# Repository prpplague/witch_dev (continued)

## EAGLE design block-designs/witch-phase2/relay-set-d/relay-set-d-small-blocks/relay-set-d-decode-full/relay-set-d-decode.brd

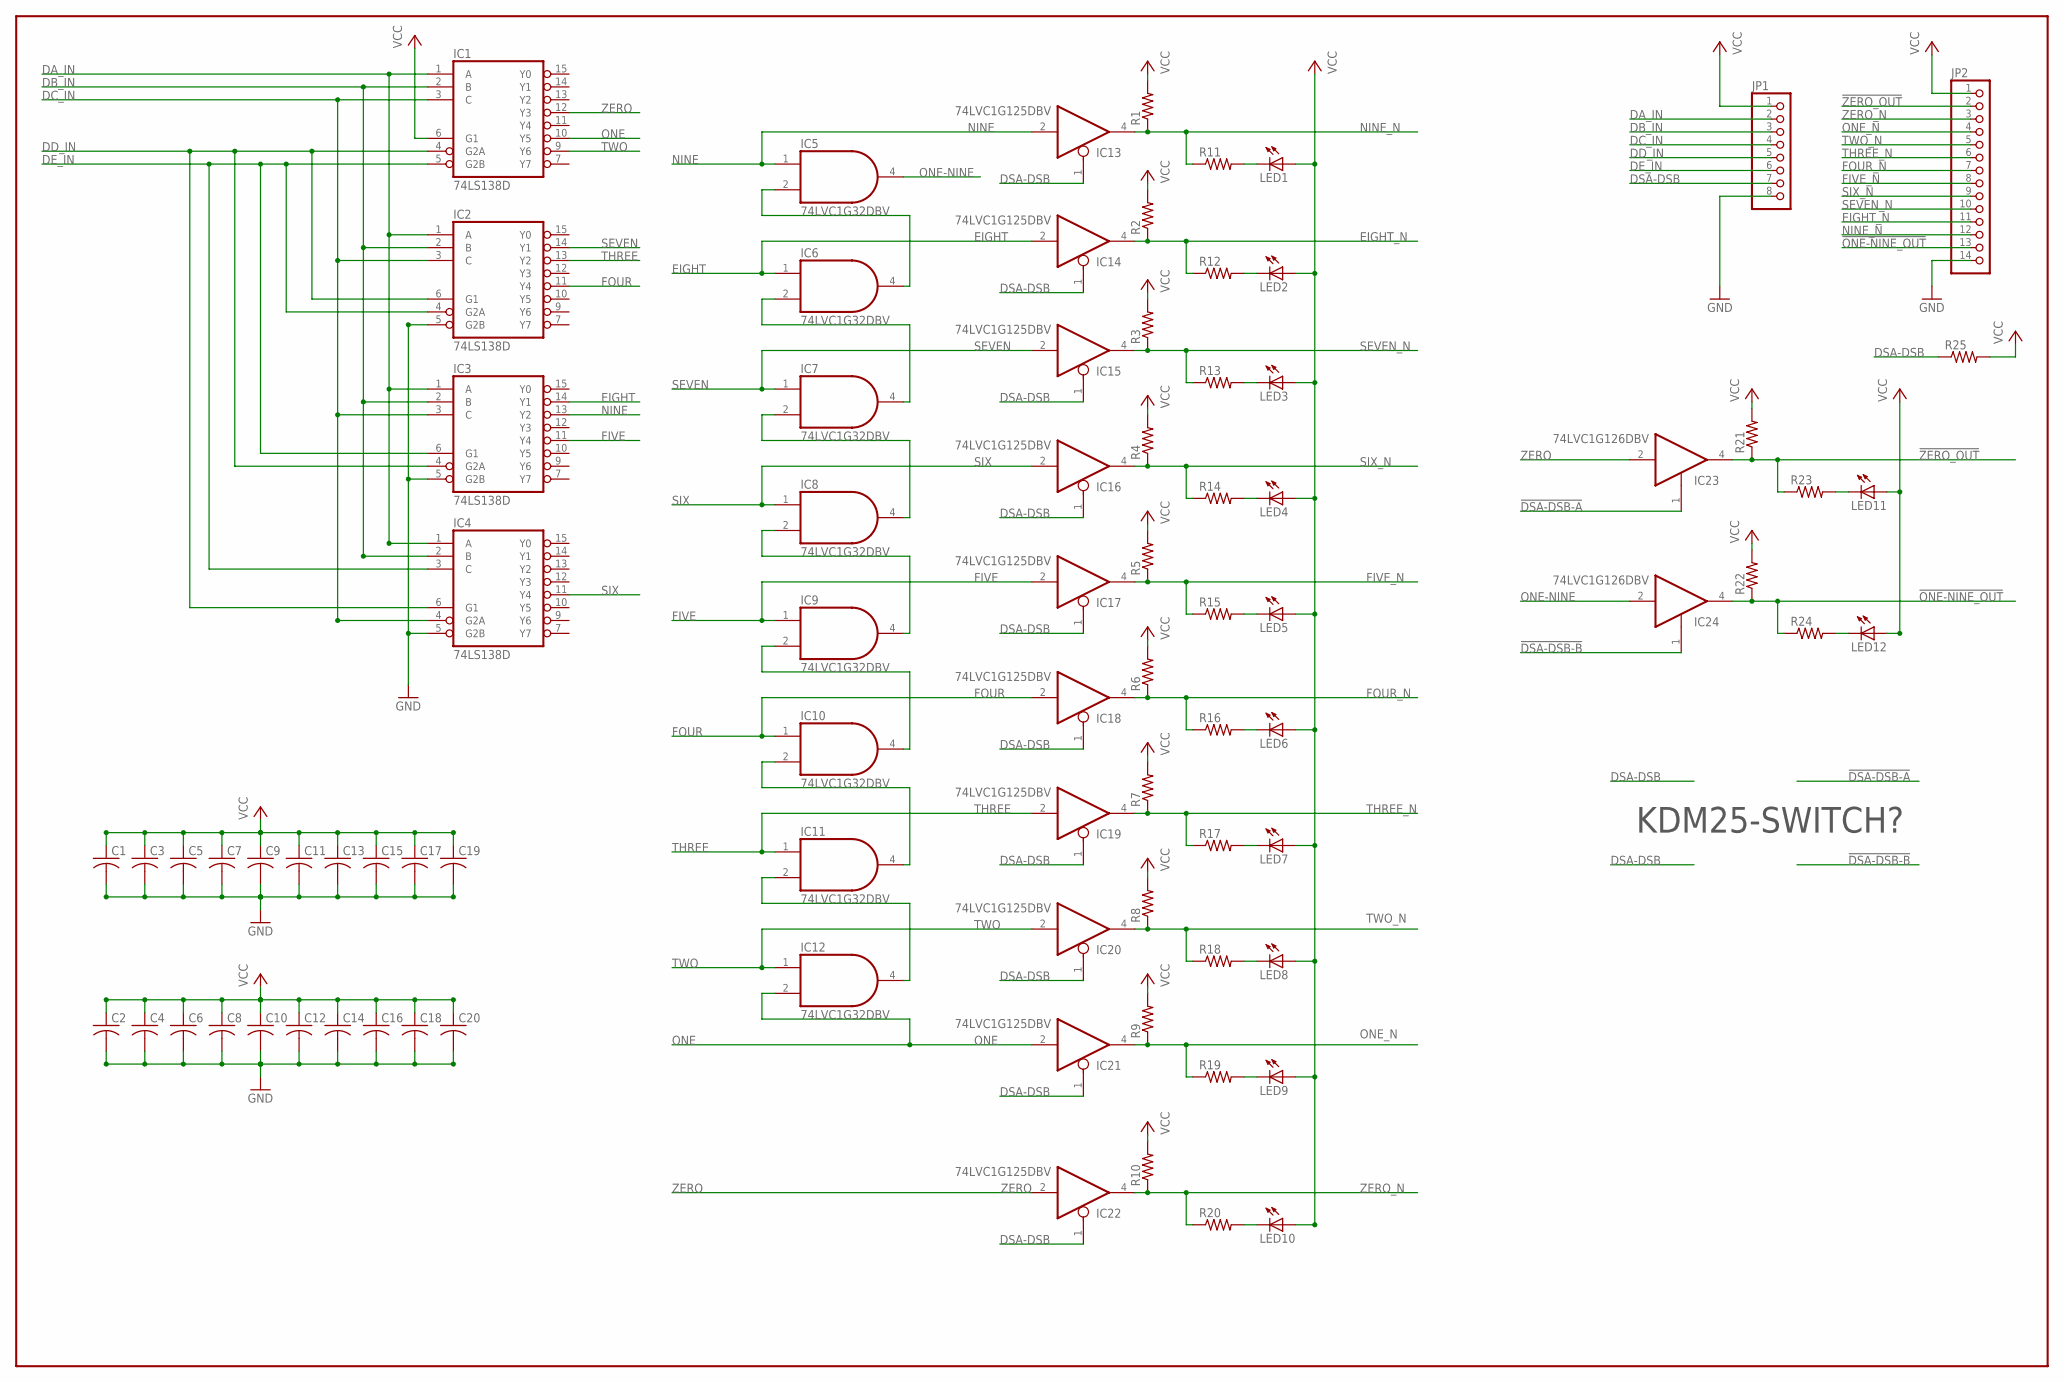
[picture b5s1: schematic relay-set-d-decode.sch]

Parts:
C1, C2, C3, C4, C5, C6, C7, C8, C9, C10, C11, C12, C13, C14, C15, C16, C17, C18, C19, C20: C-USC0805; C0805
IC1, IC2, IC3, IC4: 74LS138D; SO16
IC5, IC6, IC7, IC8, IC9, IC10, IC11, IC12: 74LVC1G32DBV; SOT23-5
IC13, IC14, IC15, IC16, IC17, IC18, IC19, IC20, IC21, IC22: 74LVC1G125DBV; SOT23-5
IC23, IC24: 74LVC1G126DBV; SOT23-5
JP1: PINHD-1X8; 1X08
JP2: PINHD-1X14; 1X14
LED1, LED2, LED3, LED4, LED5, LED6, LED7, LED8, LED9, LED10, LED11, LED12: LEDCHIP-LED0805; CHIP-LED0805
R1, R2, R3, R4, R5, R6, R7, R8, R9, R10, R11, R12, R13, R14, R15, R16, R17, R18, R19, R20, R21, R22, R23, R24, R25: R-US_R0805; R0805

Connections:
!DSA-DSB-A: IC23.1 (OE)
!DSA-DSB-B: IC24.1 (OE)
!ONE-NINE_OUT: IC24.4 (O), JP2.13, R22.1, R24.1
!ZERO_OUT: IC23.4 (O), JP2.2, R21.1, R23.1
DA_IN: IC1.1 (A), IC2.1 (A), IC3.1 (A), IC4.1 (A), JP1.2
DB_IN: IC1.2 (B), IC2.2 (B), IC3.2 (B), IC4.2 (B), JP1.3
DC_IN: IC1.3 (C), IC2.3 (C), IC3.3 (C), IC4.4 (G2A), JP1.4
DD_IN: IC1.4 (G2A), IC2.6 (G1), IC3.4 (G2A), IC4.6 (G1), JP1.5
DE_IN: IC1.5 (G2B), IC2.4 (G2A), IC3.6 (G1), IC4.3 (C), JP1.6
DSA-DSB: IC13.1 (OE), IC14.1 (OE), IC15.1 (OE), IC16.1 (OE), IC17.1 (OE), IC18.1 (OE), IC19.1 (OE), IC20.1 (OE), IC21.1 (OE), IC22.1 (OE), JP1.7, R25.1
EIGHT: IC3.14 (Y1), IC6.1 (I0), IC14.2 (I)
EIGHT_N: IC14.4 (O), JP2.11, R2.1, R12.1
FIVE: IC3.11 (Y4), IC9.1 (I0), IC17.2 (I)
FIVE_N: IC17.4 (O), JP2.8, R5.1, R15.1
FOUR: IC2.11 (Y4), IC10.1 (I0), IC18.2 (I)
FOUR_N: IC18.4 (O), JP2.7, R6.1, R16.1
GND: C1.2, C2.2, C3.2, C4.2, C5.2, C6.2, C7.2, C8.2, C9.2, C10.2, C11.2, C12.2, C13.2, C14.2, C15.2, C16.2, C17.2, C18.2, C19.2, C20.2, IC1.8 (GND), IC2.5 (G2B), IC2.8 (GND), IC3.5 (G2B), IC3.8 (GND), IC4.5 (G2B), IC4.8 (GND), IC5.3 (GND), IC6.3 (GND), IC7.3 (GND), IC8.3 (GND), IC9.3 (GND), IC10.3 (GND), IC11.3 (GND), IC12.3 (GND), IC13.3 (GND), IC14.3 (GND), IC15.3 (GND), IC16.3 (GND), IC17.3 (GND), IC18.3 (GND), IC19.3 (GND), IC20.3 (GND), IC21.3 (GND), IC22.3 (GND), IC23.3 (GND), IC24.3 (GND), JP1.8, JP2.14
unnamed: LED1.C, R11.2
unnamed: LED2.C, R12.2
unnamed: LED3.C, R13.2
unnamed: LED4.C, R14.2
unnamed: LED5.C, R15.2
unnamed: LED6.C, R16.2
unnamed: LED7.C, R17.2
unnamed: LED8.C, R18.2
unnamed: LED9.C, R19.2
unnamed: LED10.C, R20.2
unnamed: IC8.2 (I1), IC9.4 (O)
unnamed: IC9.2 (I1), IC10.4 (O)
unnamed: IC10.2 (I1), IC11.4 (O)
unnamed: IC11.2 (I1), IC12.4 (O)
unnamed: LED11.C, R23.2
unnamed: IC5.2 (I1), IC6.4 (O)
unnamed: IC6.2 (I1), IC7.4 (O)
unnamed: IC7.2 (I1), IC8.4 (O)
unnamed: LED12.C, R24.2
NINE: IC3.13 (Y2), IC5.1 (I0), IC13.2 (I)
NINE_N: IC13.4 (O), JP2.12, R1.1, R11.1
ONE: IC1.10 (Y5), IC12.2 (I1), IC21.2 (I)
ONE-NINE: IC5.4 (O), IC24.2 (I)
ONE_N: IC21.4 (O), JP2.4, R9.1, R19.1
SEVEN: IC2.14 (Y1), IC7.1 (I0), IC15.2 (I)
SEVEN_N: IC15.4 (O), JP2.10, R3.1, R13.1
SIX: IC4.11 (Y4), IC8.1 (I0), IC16.2 (I)
SIX_N: IC16.4 (O), JP2.9, R4.1, R14.1
THREE: IC2.13 (Y2), IC11.1 (I0), IC19.2 (I)
THREE_N: IC19.4 (O), JP2.6, R7.1, R17.1
TWO: IC1.9 (Y6), IC12.1 (I0), IC20.2 (I)
TWO_N: IC20.4 (O), JP2.5, R8.1, R18.1
VCC: C1.1, C2.1, C3.1, C4.1, C5.1, C6.1, C7.1, C8.1, C9.1, C10.1, C11.1, C12.1, C13.1, C14.1, C15.1, C16.1, C17.1, C18.1, C19.1, C20.1, IC1.6 (G1), IC1.16 (VCC), IC2.16 (VCC), IC3.16 (VCC), IC4.16 (VCC), IC5.5 (VCC), IC6.5 (VCC), IC7.5 (VCC), IC8.5 (VCC), IC9.5 (VCC), IC10.5 (VCC), IC11.5 (VCC), IC12.5 (VCC), IC13.5 (VCC), IC14.5 (VCC), IC15.5 (VCC), IC16.5 (VCC), IC17.5 (VCC), IC18.5 (VCC), IC19.5 (VCC), IC20.5 (VCC), IC21.5 (VCC), IC22.5 (VCC), IC23.5 (VCC), IC24.5 (VCC), JP1.1, JP2.1, LED1.A, LED2.A, LED3.A, LED4.A, LED5.A, LED6.A, LED7.A, LED8.A, LED9.A, LED10.A, LED11.A, LED12.A, R1.2, R2.2, R3.2, R4.2, R5.2, R6.2, R7.2, R8.2, R9.2, R10.2, R21.2, R22.2, R25.2
ZERO: IC1.12 (Y3), IC22.2 (I), IC23.2 (I)
ZERO_N: IC22.4 (O), JP2.3, R10.1, R20.1

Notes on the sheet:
KDM25-SWITCH?

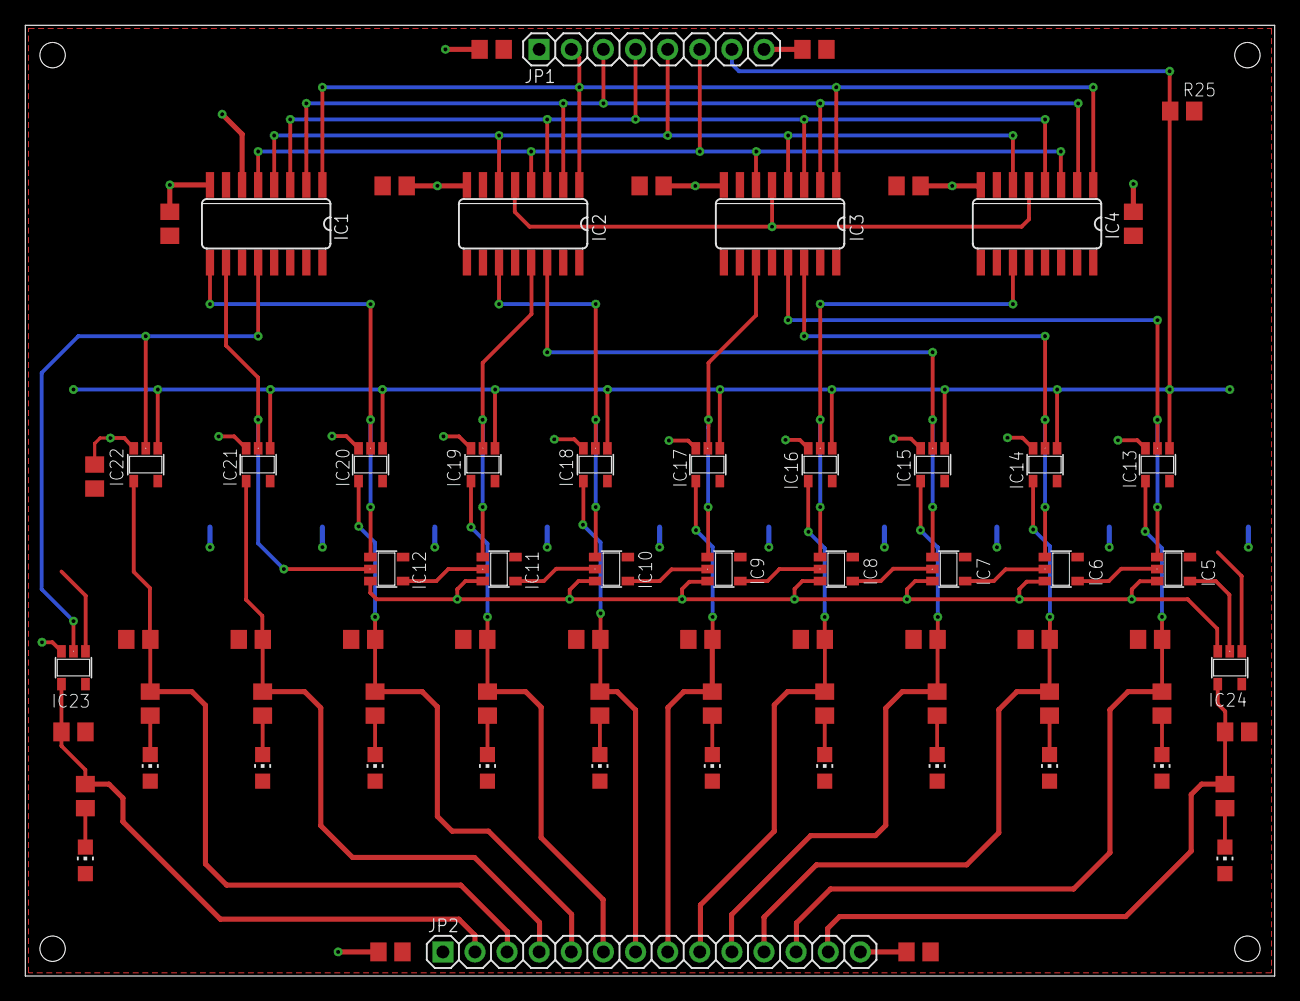
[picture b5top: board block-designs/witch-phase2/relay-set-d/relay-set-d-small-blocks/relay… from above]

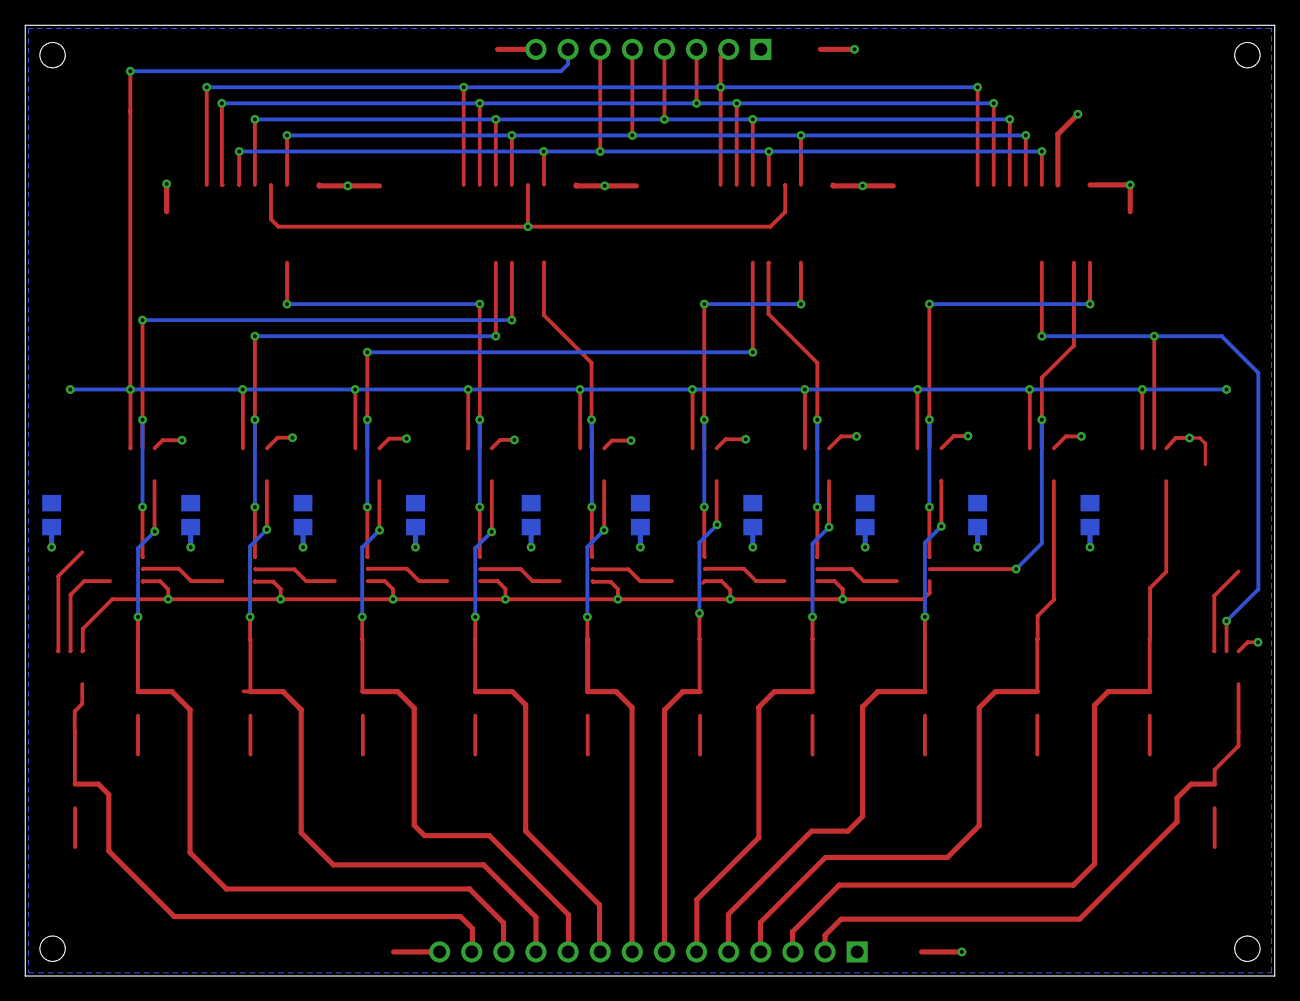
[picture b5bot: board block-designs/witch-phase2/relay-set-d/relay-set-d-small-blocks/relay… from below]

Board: 2 copper layers, 98.8 x 75.2 mm, 83 parts (10 on the bottom side), 50 nets.

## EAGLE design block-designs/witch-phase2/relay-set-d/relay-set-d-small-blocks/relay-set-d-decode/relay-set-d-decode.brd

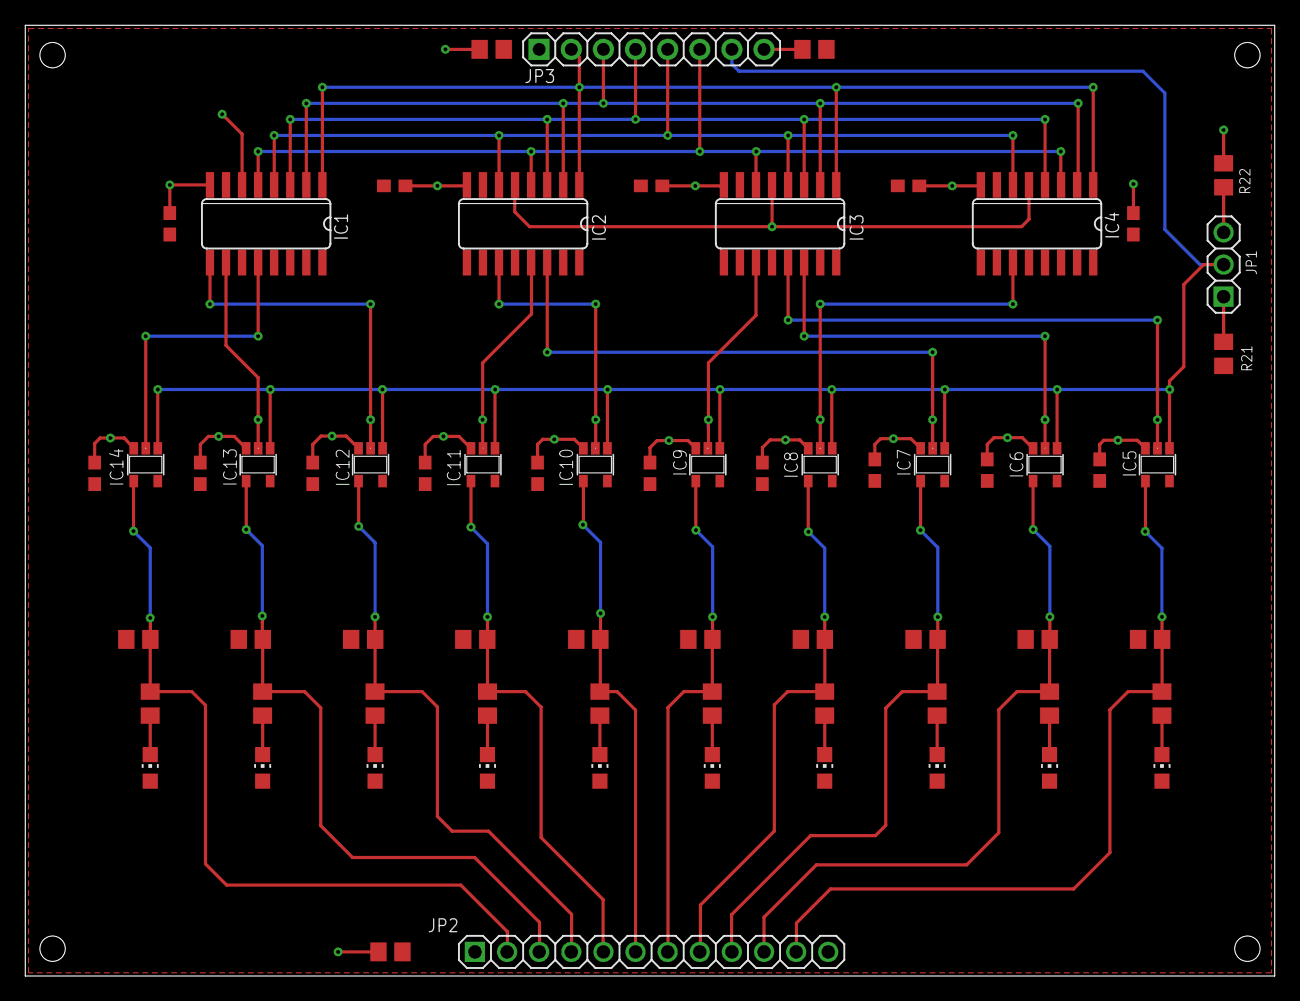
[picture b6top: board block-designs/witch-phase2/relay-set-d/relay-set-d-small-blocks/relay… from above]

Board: 2 copper layers, 98.8 x 75.2 mm, 67 parts (0 on the bottom side), 40 nets.

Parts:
C1, C2, C3, C4, C6, C8, C10, C11, C12, C13, C14, C15, C16, C17, C18: C0603
C5, C7, C9: C0805
IC1, IC2, IC3, IC4: 74LS138D; SO16
IC5, IC6, IC7, IC8, IC9, IC10, IC11, IC12, IC13, IC14: 74LVC1G125DBV; SOT23-5
JP1: 1X03
JP2: 1X12
JP3: 1X08
LED1, LED2, LED3, LED4, LED5, LED6, LED7, LED8, LED9, LED10: CHIP-LED0805
R1, R2, R3, R4, R5, R6, R7, R8, R9, R10, R11, R12, R13, R14, R15, R16, R17, R18, R19, R20, R21, R22: R0805

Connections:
DA_IN: IC1.1, IC2.1, IC3.1, IC4.1, JP3.2
DB_IN: IC1.2, IC2.2, IC3.2, IC4.2, JP3.3
DC_IN: IC1.3, IC2.3, IC3.3, IC4.4, JP3.4
DD_IN: IC1.4, IC2.6, IC3.4, IC4.6, JP3.5
DE_IN: IC1.5, IC2.4, IC3.6, IC4.3, JP3.6
DSA-DSB: IC5.1, IC6.1, IC7.1, IC8.1, IC9.1, IC10.1, IC11.1, IC12.1, IC13.1, IC14.1, JP1.2, JP3.7
EIGHT: IC3.14, IC6.2
EIGHT_N: IC6.4, JP2.10, R2.1, R12.1
FIVE: IC3.11, IC9.2
FIVE_N: IC9.4, JP2.7, R5.1, R15.1
FOUR: IC2.11, IC10.2
FOUR_N: IC10.4, JP2.6, R6.1, R16.1
GND: C1.2, C2.2, C3.2, C4.2, C5.2, C6.2, C7.2, C8.2, C9.2, C10.2, C11.2, C12.2, C13.2, C14.2, C15.2, C16.2, C17.2, C18.2, IC1.8, IC2.5, IC2.8, IC3.5, IC3.8, IC4.5, IC4.8, IC5.3, IC6.3, IC7.3, IC8.3, IC9.3, IC10.3, IC11.3, IC12.3, IC13.3, IC14.3, JP2.1, JP2.12, JP3.8, R22.1
unnamed: LED1.C, R11.2
unnamed: LED2.C, R12.2
unnamed: LED3.C, R13.2
unnamed: LED4.C, R14.2
unnamed: LED5.C, R15.2
unnamed: LED6.C, R16.2
unnamed: LED7.C, R17.2
unnamed: LED8.C, R18.2
unnamed: LED9.C, R19.2
unnamed: LED10.C, R20.2
unnamed: JP1.1, R21.1
unnamed: JP1.3, R22.2
NINE: IC3.13, IC5.2
NINE_N: IC5.4, JP2.11, R1.1, R11.1
ONE: IC1.10, IC13.2
ONE_N: IC13.4, JP2.3, R9.1, R19.1
SEVEN: IC2.14, IC7.2
SEVEN_N: IC7.4, JP2.9, R3.1, R13.1
SIX: IC4.11, IC8.2
SIX_N: IC8.4, JP2.8, R4.1, R14.1
THREE: IC2.13, IC11.2
THREE_N: IC11.4, JP2.5, R7.1, R17.1
TWO: IC1.9, IC12.2
TWO_N: IC12.4, JP2.4, R8.1, R18.1
VCC: C1.1, C2.1, C3.1, C4.1, C5.1, C6.1, C7.1, C8.1, C9.1, C10.1, C11.1, C12.1, C13.1, C14.1, C15.1, C16.1, C17.1, C18.1, IC1.6, IC1.16, IC2.16, IC3.16, IC4.16, IC5.5, IC6.5, IC7.5, IC8.5, IC9.5, IC10.5, IC11.5, IC12.5, IC13.5, IC14.5, JP3.1, LED1.A, LED2.A, LED3.A, LED4.A, LED5.A, LED6.A, LED7.A, LED8.A, LED9.A, LED10.A, R1.2, R2.2, R3.2, R4.2, R5.2, R6.2, R7.2, R8.2, R9.2, R10.2, R21.2
ZERO: IC1.12, IC14.2
ZERO_N: IC14.4, JP2.2, R10.1, R20.1

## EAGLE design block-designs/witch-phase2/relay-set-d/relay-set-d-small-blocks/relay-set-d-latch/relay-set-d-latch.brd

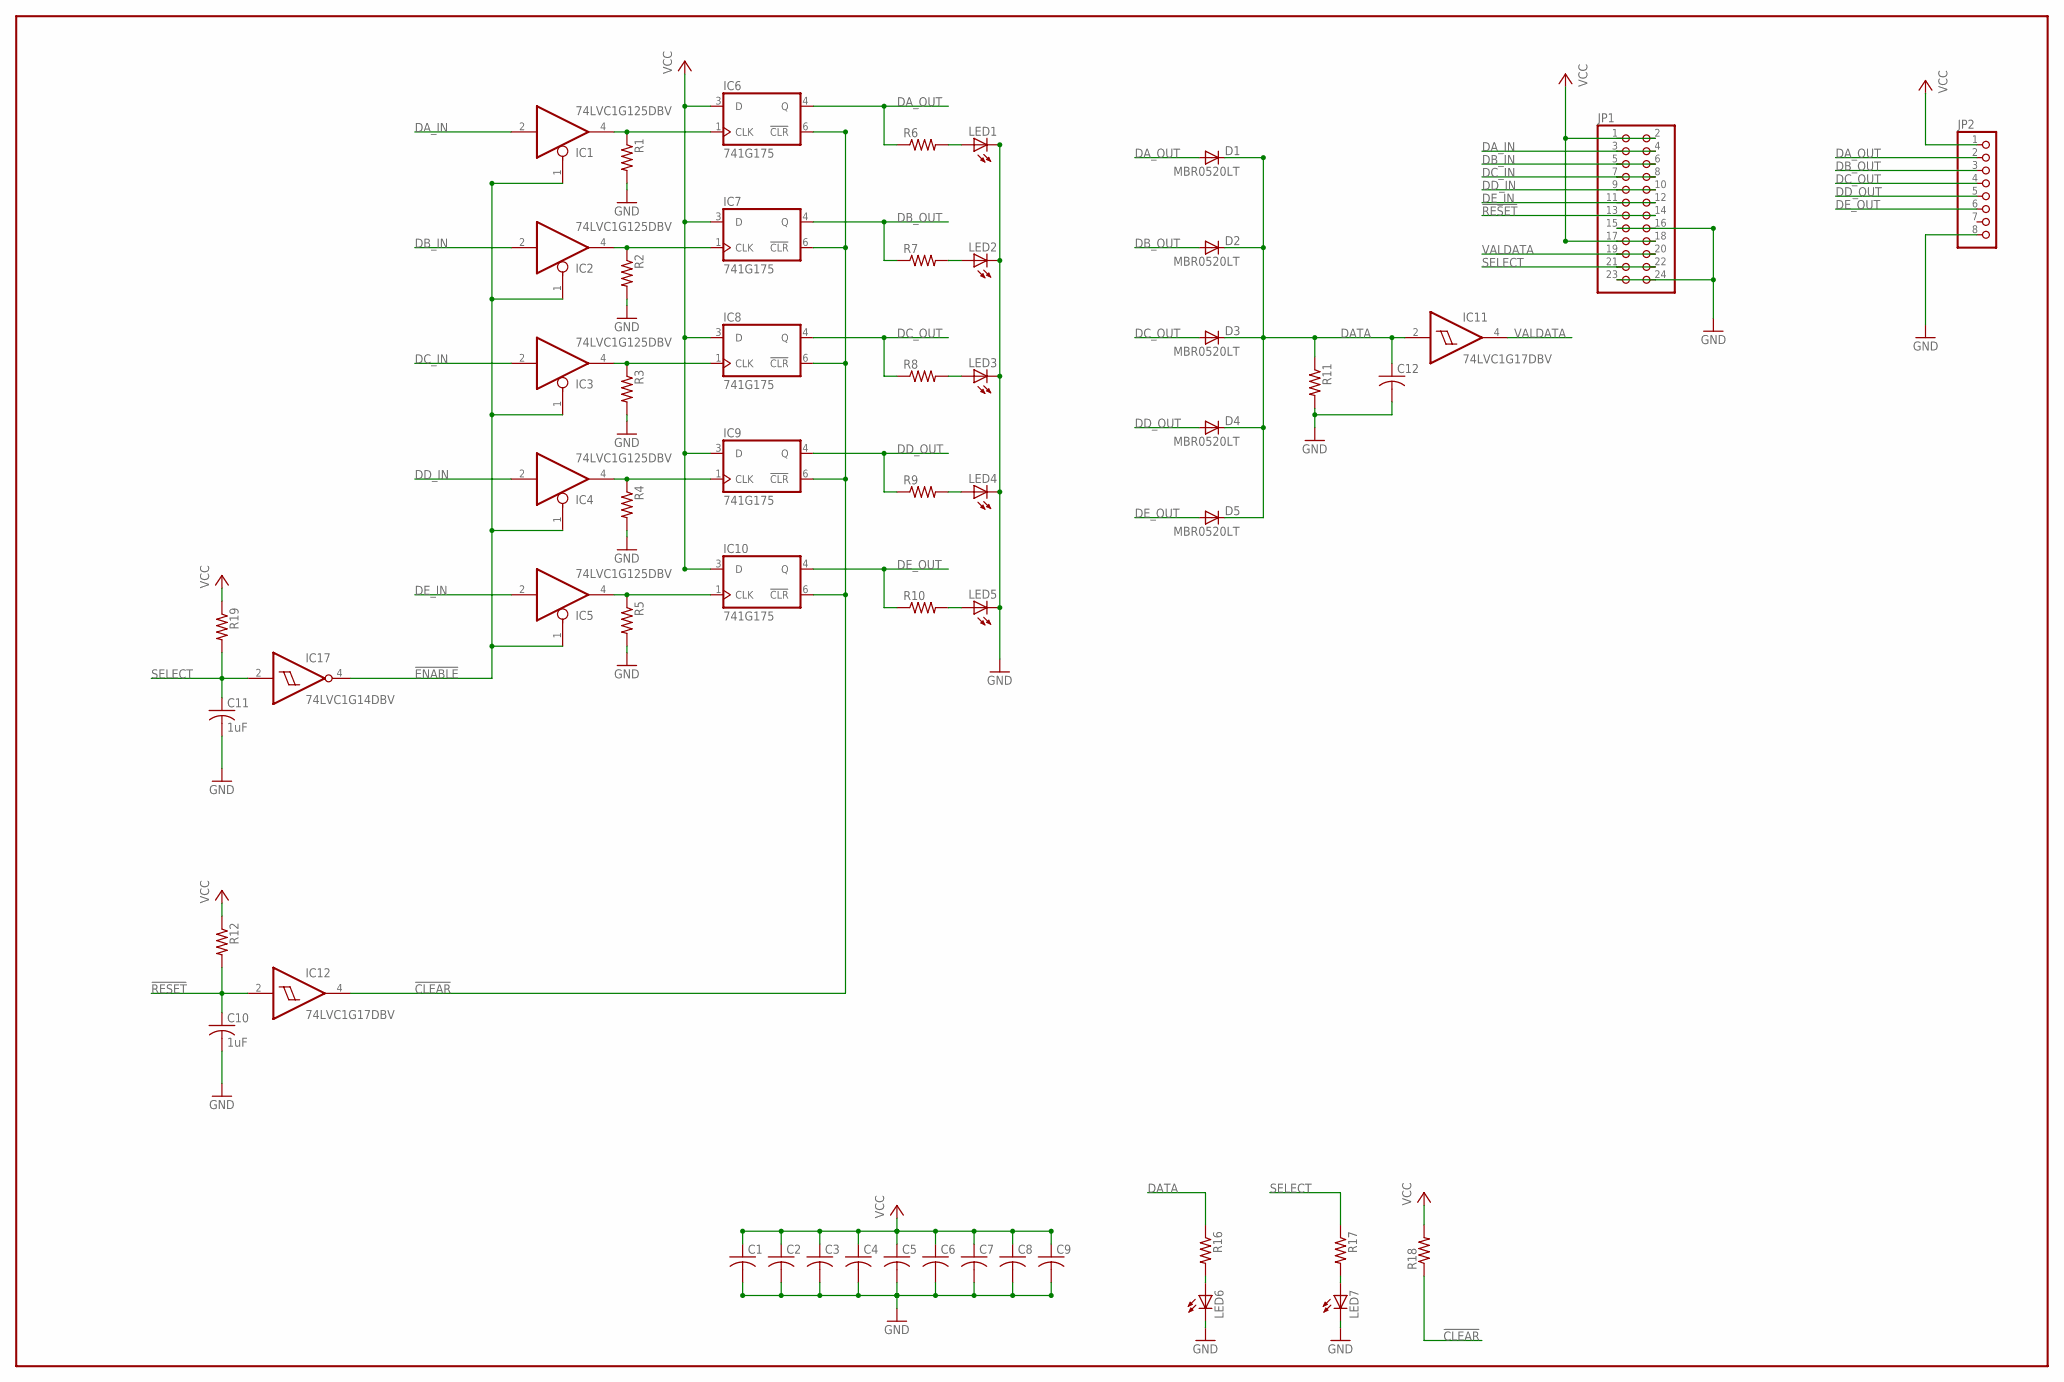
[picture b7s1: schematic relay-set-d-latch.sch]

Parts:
C1, C2, C3, C4, C12: C-USC0805; C0805
C5, C6, C7, C8, C9: C-USC0603K; C0603K
C10, C11: 1uF; C0603K
D1, D2, D3, D4, D5: MBR0520LT; SOD123
IC1, IC2, IC3, IC4, IC5: 74LVC1G125DBV; SOT23-5
IC6, IC7, IC8, IC9, IC10: 741G175; DBV_R-PDSO-G6
IC11, IC12: 74LVC1G17DBV; SOT23-5
IC17: 74LVC1G14DBV; SOT23-5
JP1: PINHD-2X12; 2X12
JP2: PINHD-1X8; 1X08
LED1, LED2, LED3, LED4, LED5, LED6, LED7: LEDCHIP-LED0805; CHIP-LED0805
R1, R2, R3, R4, R5, R6, R7, R8, R9, R10, R11, R12, R16, R17, R18, R19: R-US_R0805; R0805

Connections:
!CLEAR: IC6.6 (!CLR), IC7.6 (!CLR), IC8.6 (!CLR), IC9.6 (!CLR), IC10.6 (!CLR), IC12.4 (O), R18.1
!ENABLE: IC1.1 (OE), IC2.1 (OE), IC3.1 (OE), IC4.1 (OE), IC5.1 (OE), IC17.4 (O)
!RESET: C10.1, IC12.2 (I), JP1.13, JP1.14, R12.2
DA: IC1.4 (O), IC6.1 (CLK), R1.1
DATA: C12.1, D1.C, D2.C, D3.C, D4.C, D5.C, IC11.2 (I), R11.1, R16.1
DA_IN: IC1.2 (I), JP1.3, JP1.4
DA_OUT: D1.A, IC6.4 (Q), JP2.2, R6.1
DB: IC2.4 (O), IC7.1 (CLK), R2.1
DB_IN: IC2.2 (I), JP1.5, JP1.6
DB_OUT: D2.A, IC7.4 (Q), JP2.3, R7.1
DC: IC3.4 (O), IC8.1 (CLK), R3.1
DC_IN: IC3.2 (I), JP1.7, JP1.8
DC_OUT: D3.A, IC8.4 (Q), JP2.4, R8.1
DD: IC4.4 (O), IC9.1 (CLK), R4.1
DD_IN: IC4.2 (I), JP1.9, JP1.10
DD_OUT: D4.A, IC9.4 (Q), JP2.5, R9.1
DE: IC5.4 (O), IC10.1 (CLK), R5.1
DE_IN: IC5.2 (I), JP1.11, JP1.12
DE_OUT: D5.A, IC10.4 (Q), JP2.6, R10.1
GND: C1.2, C2.2, C3.2, C4.2, C5.2, C6.2, C7.2, C8.2, C9.2, C10.2, C11.2, C12.2, IC1.3 (GND), IC2.3 (GND), IC3.3 (GND), IC4.3 (GND), IC5.3 (GND), IC6.2 (GND), IC7.2 (GND), IC8.2 (GND), IC9.2 (GND), IC10.2 (GND), IC11.3 (GND), IC12.3 (GND), IC17.3 (GND), JP1.15, JP1.16, JP1.23, JP1.24, JP2.8, LED1.C, LED2.C, LED3.C, LED4.C, LED5.C, LED6.C, LED7.C, R1.2, R2.2, R3.2, R4.2, R5.2, R11.2
unnamed: LED1.A, R6.2
unnamed: LED2.A, R7.2
unnamed: LED3.A, R8.2
unnamed: LED7.A, R17.2
unnamed: LED6.A, R16.2
unnamed: LED4.A, R9.2
unnamed: LED5.A, R10.2
SELECT: C11.1, IC17.2 (I), JP1.21, JP1.22, R17.1, R19.2
VALDATA: IC11.4 (O), JP1.19, JP1.20
VCC: C1.1, C2.1, C3.1, C4.1, C5.1, C6.1, C7.1, C8.1, C9.1, IC1.5 (VCC), IC2.5 (VCC), IC3.5 (VCC), IC4.5 (VCC), IC5.5 (VCC), IC6.3 (D), IC6.5 (VCC), IC7.3 (D), IC7.5 (VCC), IC8.3 (D), IC8.5 (VCC), IC9.3 (D), IC9.5 (VCC), IC10.3 (D), IC10.5 (VCC), IC11.5 (VCC), IC12.5 (VCC), IC17.5 (VCC), JP1.1, JP1.2, JP1.17, JP1.18, JP2.1, R12.1, R18.2, R19.1

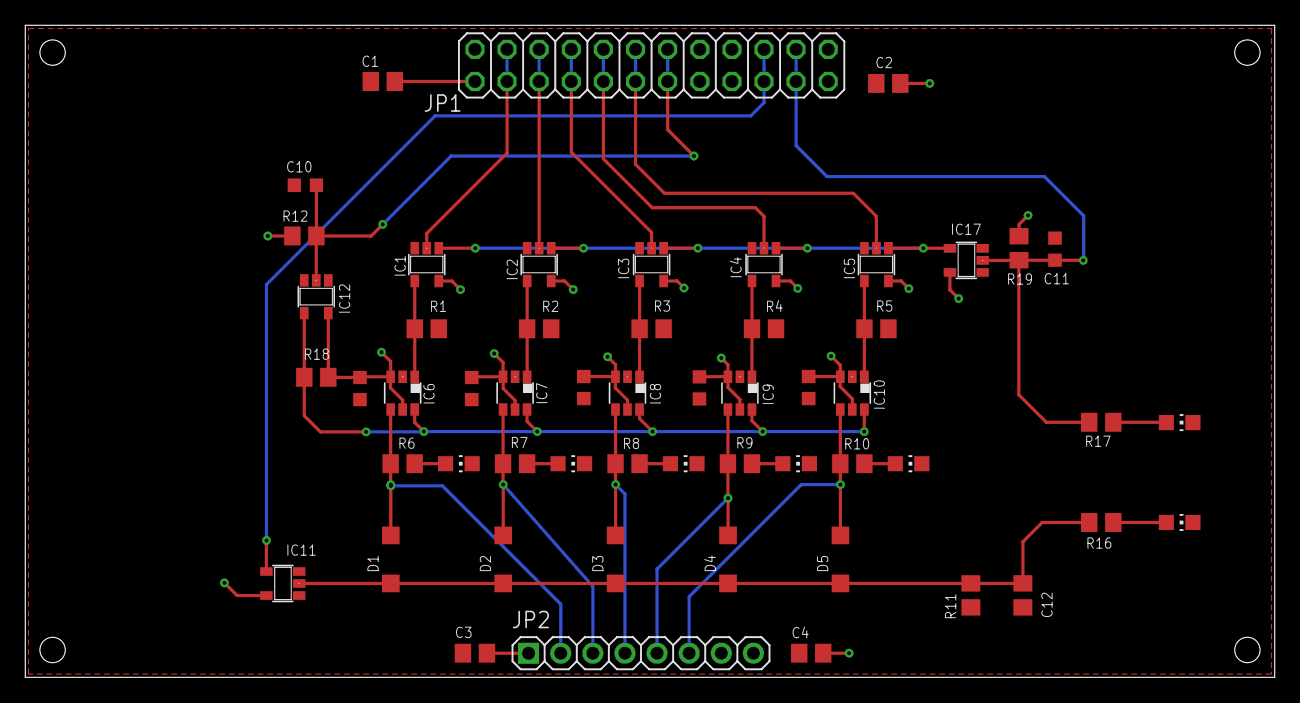
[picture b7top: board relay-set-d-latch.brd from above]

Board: 2 copper layers, 98.8 x 51.6 mm, 55 parts (0 on the bottom side), 30 nets.

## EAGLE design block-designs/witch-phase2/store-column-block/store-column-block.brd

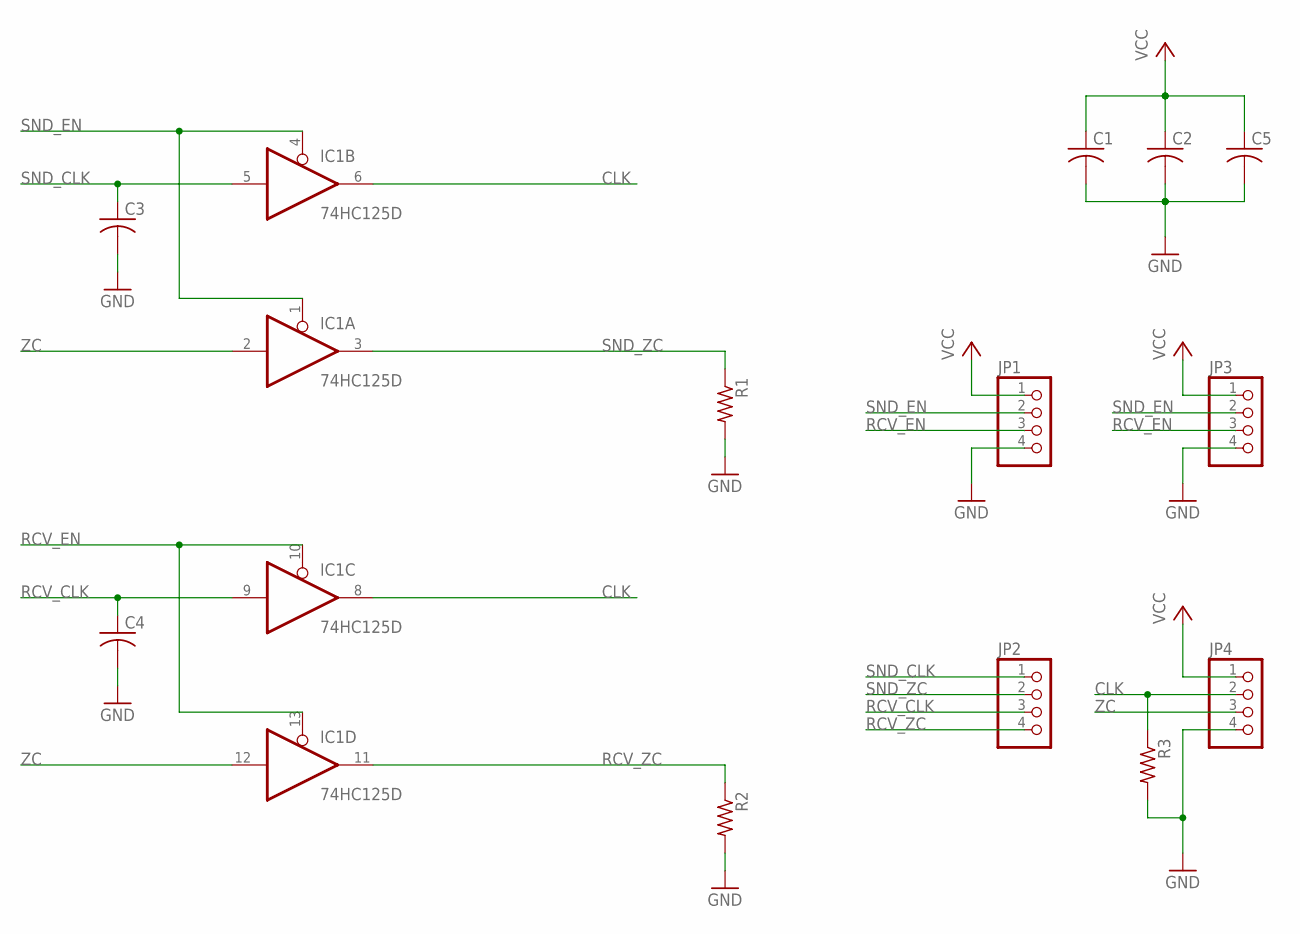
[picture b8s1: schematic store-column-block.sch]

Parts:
C1, C2, C3, C4, C5: C-USC0603K; C0603K
IC1: 74HC125D; SO14
JP1, JP2, JP3, JP4: PINHD-1X4; 1X04
R1, R2, R3: R-US_R0603; R0603

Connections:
CLK: IC1.6 (O), IC1.8 (O), JP4.2, R3.1
GND: C1.2, C2.2, C3.2, C4.2, C5.2, IC1.7 (GND), JP1.4, JP3.4, JP4.4, R1.2, R2.2, R3.2
RCV_CLK: C4.1, IC1.9 (I), JP2.3
RCV_EN: IC1.10 (OE), IC1.13 (OE), JP1.3, JP3.3
RCV_ZC: IC1.11 (O), JP2.4, R2.1
SND_CLK: C3.1, IC1.5 (I), JP2.1
SND_EN: IC1.1 (OE), IC1.4 (OE), JP1.2, JP3.2
SND_ZC: IC1.3 (O), JP2.2, R1.1
VCC: C1.1, C2.1, C5.1, IC1.14 (VCC), JP1.1, JP3.1, JP4.1
ZC: IC1.2 (I), IC1.12 (I), JP4.3

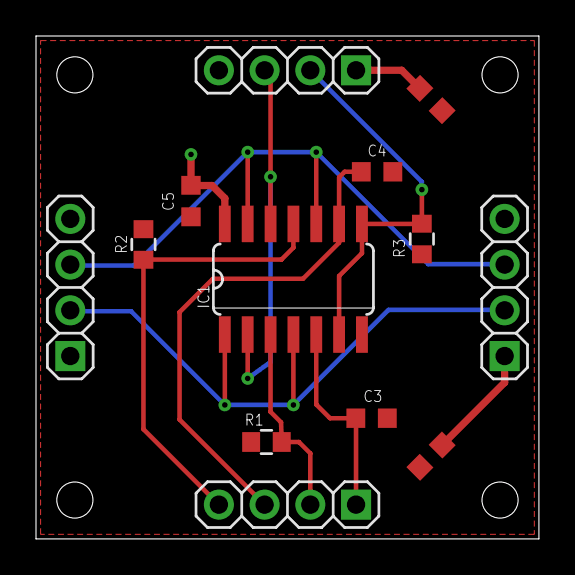
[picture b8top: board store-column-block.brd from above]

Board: 2 copper layers, 27.9 x 27.9 mm, 13 parts (0 on the bottom side), 10 nets.
